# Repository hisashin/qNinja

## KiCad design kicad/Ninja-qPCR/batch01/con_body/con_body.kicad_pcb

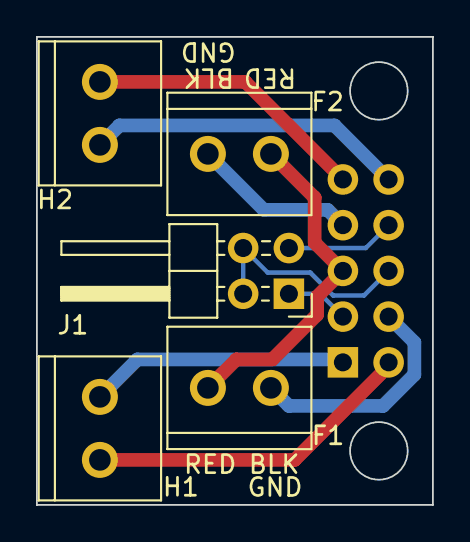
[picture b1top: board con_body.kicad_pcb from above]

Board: 2 copper layers, 22.0 x 26.0 mm, 6 parts (1 on the bottom side), 10 nets.

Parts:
F1, F2: Screw_Terminal_01x02; TB_SeeedOPL_320110028
H1, H2: Screw_Terminal_01x02; TB_SeeedOPL_320110028
J1: Conn_01x04_Male; Pin_Header_Angled_2x02_Pitch2.54mm
U1: Conn_02x05; Pin_Header_Straight_2x05_Pitch2.54mm

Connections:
FAN_BLACK_GND1: F1.2, U1.4
FAN_BLACK_GND2: F2.2, U1.7
FAN_RED_VCC: F1.1, F2.1, U1.5
GND: J1.2, J1.4, U1.6
HEATER1A: H1.1, U1.1
HEATER1B: H1.2, U1.2
HEATER2A: H2.1, U1.9
HEATER2B: H2.2, U1.10
THERM_EXT3: J1.3, U1.8
THERM_WELL: J1.1, U1.3

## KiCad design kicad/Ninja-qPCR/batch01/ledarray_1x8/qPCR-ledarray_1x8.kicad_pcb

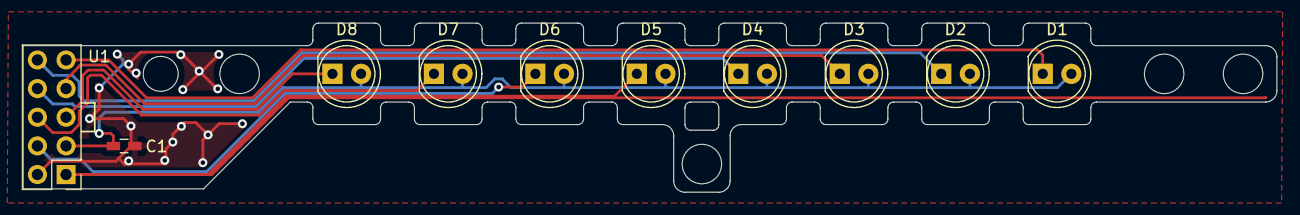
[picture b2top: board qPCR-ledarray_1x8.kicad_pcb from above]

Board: 2 copper layers, 111.2 x 15.0 mm, 10 parts (0 on the bottom side), 10 nets.

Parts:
C1: C; C_0603_HandSoldering
D1, D2, D3, D4, D5, D6, D7, D8: LED; LED_D5.0mm
U1: Conn_02x05; Pin_Header_Straight_2x05_Pitch2.54mm

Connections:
GND: C1.2, U1.2
OUT1: D1.1, U1.9
OUT2: D2.1, U1.10
OUT3: D3.1, U1.7
OUT4: D4.1, U1.8
OUT5: D5.1, U1.1
OUT6: D6.1, U1.4
OUT7: D7.1, U1.6
OUT8: D8.1, U1.5
VCC: C1.1, D1.2, D2.2, D3.2, D4.2, D5.2, D6.2, D7.2, D8.2, U1.3

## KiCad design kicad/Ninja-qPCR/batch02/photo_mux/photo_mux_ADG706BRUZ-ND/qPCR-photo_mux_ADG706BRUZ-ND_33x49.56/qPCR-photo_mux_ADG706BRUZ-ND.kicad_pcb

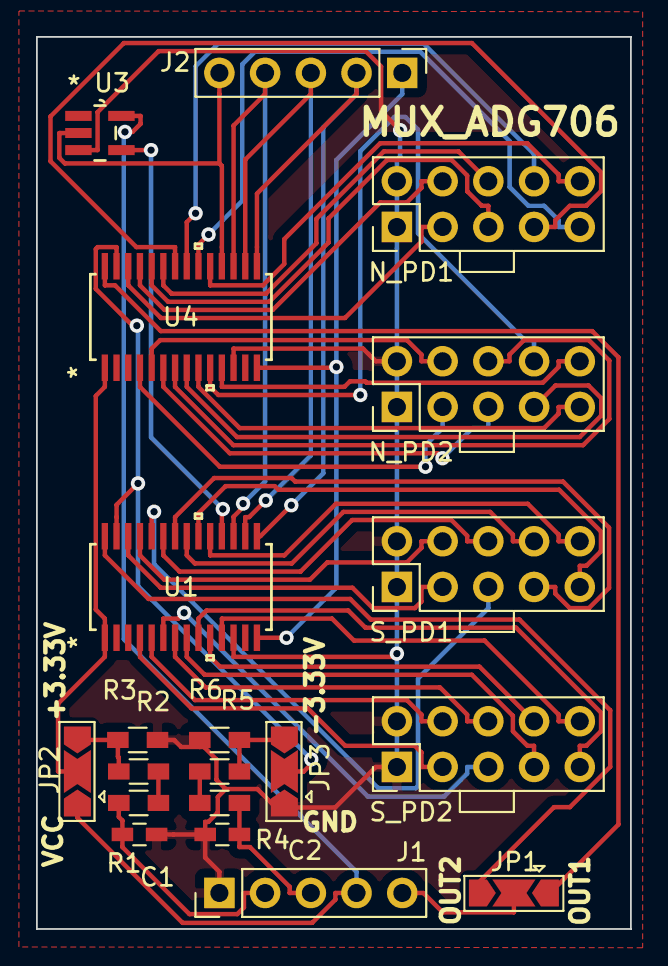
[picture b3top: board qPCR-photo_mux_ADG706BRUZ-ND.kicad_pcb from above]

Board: 2 copper layers, 33.0 x 49.6 mm, 20 parts (0 on the bottom side), 51 nets.

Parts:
C1, C2: C; C_0603_HandSoldering
J1, J2: Conn_01x05_Male; Pin_Header_Straight_1x05_Pitch2.54mm
JP1, JP2, JP3: Jumper_3_Open; SolderJumper-3_P2.0mm_Open_TrianglePad1.0x1.5mm
N_PD1, N_PD2: Conn_02x05; Con_2x05
R1, R2, R3, R4, R5, R6: R; R_0603_HandSoldering
S_PD1, S_PD2: Conn_02x05; Con_2x05
U1, U4: ADG706BRUZ
U3: SN74LVC1G04DBVR

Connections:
+10V: C1.1, J1.2, R1.1
-10V: C2.1, J1.3, R4.1
/+3.33V: JP2.3, R2.2, R3.1
/-3.33V: JP3.3, R5.2, R6.1
/MUX_SELECT_INV: U1.18, U3.4
/PD_MUX_OUT1: JP1.1, U4.28
/PD_MUX_OUT2: JP1.3, U1.28
/VDD: JP2.2, U1.1, U4.1
/VSS: JP3.2, U1.27, U4.27
ADDRESSA0: J2.4, U1.17, U4.17
ADDRESSA1: J2.3, U1.16, U4.16
ADDRESSA2: J2.2, U1.15, U4.15
ADDRESSA3: J2.1, U1.14, U4.14
GND: C1.2, C2.2, J1.1, JP3.1, N_PD1.1, N_PD1.2, N_PD2.1, N_PD2.2, R3.2, R6.2, S_PD1.1, S_PD1.2, S_PD2.1, S_PD2.2, U1.12, U3.3, U4.12
MUX_SELECT: J2.5, U3.2, U4.18
N_PD1_OUT1: N_PD1.10, U4.19
N_PD1_OUT2: N_PD1.9, U4.20
N_PD1_OUT3: N_PD1.8, U4.21
N_PD1_OUT4: N_PD1.7, U4.22
N_PD1_OUT5: N_PD1.6, U4.23
N_PD1_OUT6: N_PD1.5, U4.24
N_PD1_OUT7: N_PD1.4, U4.25
N_PD1_OUT8: N_PD1.3, U4.26
N_PD1_OUT9: N_PD2.10, U4.11
N_PD1_OUT10: N_PD2.8, U4.10
N_PD1_OUT11: N_PD2.9, U4.9
N_PD1_OUT12: N_PD2.7, U4.8
N_PD1_OUT13: N_PD2.6, U4.7
N_PD1_OUT14: N_PD2.5, U4.6
N_PD1_OUT15: N_PD2.4, U4.5
N_PD1_OUT16: N_PD2.3, U4.4
unnamed: R1.2, R2.1
unnamed: R4.2, R5.1
PD_MUX_OUT: J1.5, JP1.2
S_PD1_OUT1: S_PD1.10, U1.19
S_PD1_OUT2: S_PD1.9, U1.20
S_PD1_OUT3: S_PD1.8, U1.21
S_PD1_OUT4: S_PD1.7, U1.22
S_PD1_OUT5: S_PD1.6, U1.23
S_PD1_OUT6: S_PD1.5, U1.24
S_PD1_OUT7: S_PD1.4, U1.25
S_PD1_OUT8: S_PD1.3, U1.26
S_PD1_OUT9: S_PD2.10, U1.11
S_PD1_OUT10: S_PD2.8, U1.10
S_PD1_OUT11: S_PD2.9, U1.9
S_PD1_OUT12: S_PD2.7, U1.8
S_PD1_OUT13: S_PD2.6, U1.7
S_PD1_OUT14: S_PD2.5, U1.6
S_PD1_OUT15: S_PD2.4, U1.5
S_PD1_OUT16: S_PD2.3, U1.4
VCC_LOGIC: J1.4, JP2.1, U3.5

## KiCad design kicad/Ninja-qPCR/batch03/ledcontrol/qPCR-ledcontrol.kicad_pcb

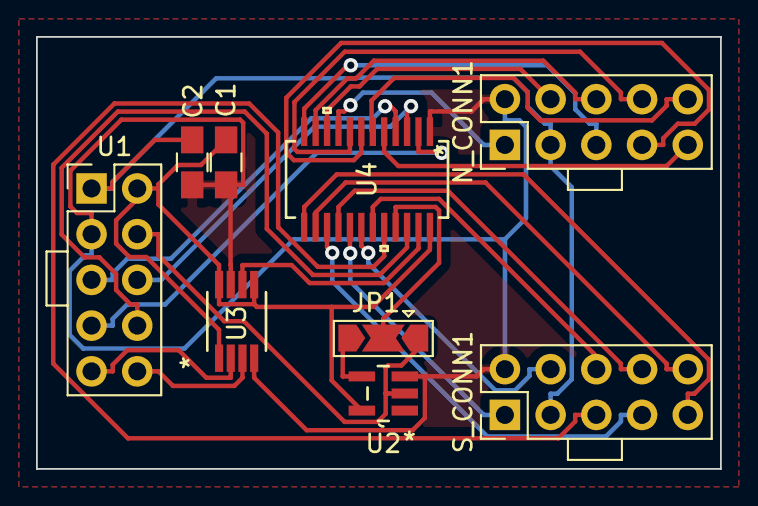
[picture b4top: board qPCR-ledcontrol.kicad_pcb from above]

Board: 2 copper layers, 38.0 x 24.0 mm, 9 parts (0 on the bottom side), 29 nets.

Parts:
C1, C2: C; C_0805_HandSoldering
JP1: Jumper_3_Open; SolderJumper-3_P2.0mm_Open_TrianglePad1.0x1.5mm
N_CONN1: Conn_02x05; Con_2x05
S_CONN1: Conn_02x05; Con_2x05
U1: Conn_02x05; Con_2x05
U2: SN74LVC1G04DBVR
U3: MCP4551T-502E_MS; MCP4551T-502E&slash_MS
U4: TLC59281DBQR

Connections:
/LED_IREF: U3.6, U4.23
GND: C1.2, C2.2, N_CONN1.2, S_CONN1.2, U1.3, U2.3, U3.4, U3.7, U4.1
I2C_SCL: U1.9, U3.2
I2C_SDA: U1.10, U3.3
LED_BLANK: JP1.2, U4.21
LED_LAT: U1.5, U4.4
LED_PWM: JP1.1, U1.4, U2.2
LED_SPI_MISO: U1.8, U4.22
LED_SPI_MOSI: U1.7, U4.2
LED_SPI_SCLK: U1.6, U4.3
N_LED_OUT1: N_CONN1.9, U4.5
N_LED_OUT2: N_CONN1.10, U4.6
N_LED_OUT3: N_CONN1.7, U4.7
N_LED_OUT4: N_CONN1.8, U4.8
N_LED_OUT5: N_CONN1.1, U4.9
N_LED_OUT6: N_CONN1.4, U4.10
N_LED_OUT7: N_CONN1.6, U4.11
N_LED_OUT8: N_CONN1.5, U4.12
unnamed: JP1.3, U2.4
S_LED_OUT1: S_CONN1.9, U4.13
S_LED_OUT2: S_CONN1.10, U4.14
S_LED_OUT3: S_CONN1.7, U4.15
S_LED_OUT4: S_CONN1.8, U4.16
S_LED_OUT5: S_CONN1.1, U4.17
S_LED_OUT6: S_CONN1.4, U4.18
S_LED_OUT7: S_CONN1.6, U4.19
S_LED_OUT8: S_CONN1.5, U4.20
VCC_LED: C2.1, N_CONN1.3, S_CONN1.3, U1.1
VCC_LOGIC: C1.1, U1.2, U2.5, U3.1, U3.5, U3.8, U4.24

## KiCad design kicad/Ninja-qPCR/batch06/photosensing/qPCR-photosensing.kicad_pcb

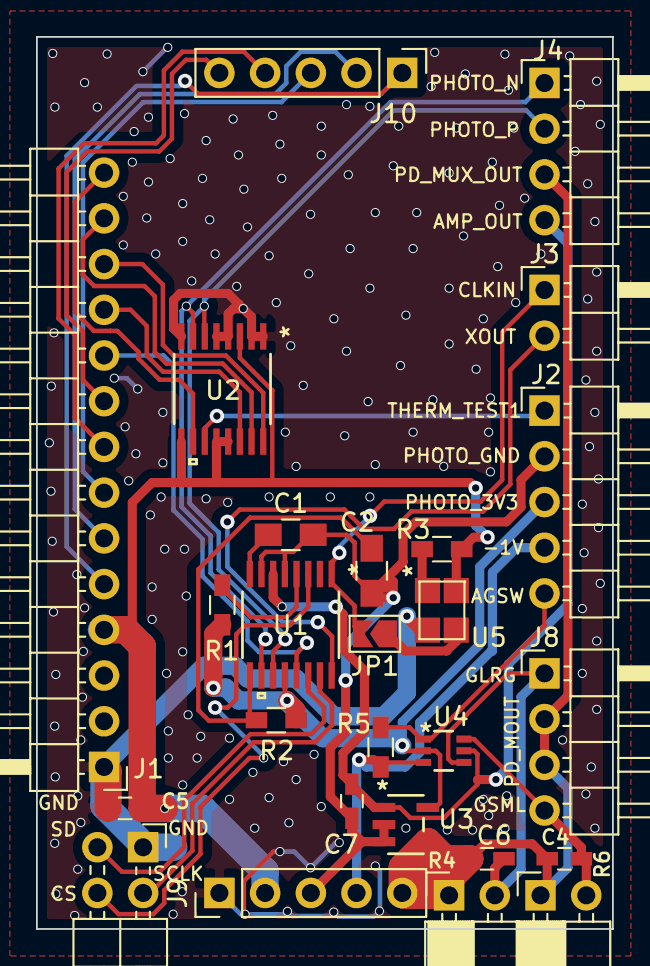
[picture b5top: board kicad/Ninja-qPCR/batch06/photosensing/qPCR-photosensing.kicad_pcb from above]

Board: 2 copper layers, 32.0 x 49.6 mm, 26 parts (0 on the bottom side), 33 nets.

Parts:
C1: 1uF; C_0805_HandSoldering
C2: 10uF; C_0805_HandSoldering
C4, C6: 22pF; C_0603_HandSoldering
C5, C7: 0.1uF; C_0603_HandSoldering
J1: Conn_01x14_Male; Pin_Header_Angled_1x14_Pitch2.54mm
J2: Conn_01x05_Male; Pin_Header_Angled_1x05_Pitch2.54mm
J3: Conn_01x02_Male; Pin_Header_Angled_1x02_Pitch2.54mm
J4, J8: Conn_01x04_Male; Pin_Header_Angled_1x04_Pitch2.54mm
J9, J10: Conn_01x05_Female; Pin_Header_Straight_1x05_Pitch2.54mm
JP1: Jumper; SolderJumper-2_P1.3mm_Open_TrianglePad1.0x1.5mm
JSPI1: Conn_01x04_Male; Pin_Header_Angled_2x02_Pitch2.54mm
R1, R2, R3: 10K; R_0603_HandSoldering
R4, R6: R; Socket_Strip_Angled_1x02_Pitch2.54mm
R5: R; R_0603_HandSoldering
U1: ADA2200ARUZ
U2: ADS1219IPWR
U3: AD8605ARTZ-R2
U4: TS5A9411DCKR
U5: COM1305-0.032768-EXT-T-TR

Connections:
-1V: J2.4, J9.4, R5.2, U4.3
/AMP_GAIN_SW: J2.5, R5.1, U4.1
/AMP_OUT: C7.2, J4.4, U1.6, U3.1, U4.5
/GAIN_LARGE: C6.1, J8.1, R4.2, U4.4
/GAIN_SMALL: C4.1, J8.4, R6.2, U4.6
/PHOTO_OUT_N: J4.1, U1.10, U2.7
/PHOTO_OUT_P: J4.2, U1.11, U2.6
ADC_DRDY: J1.11, U2.14
CLKIN: J3.1, JP1.2, U1.1
DEMOD_SPI_CS: JSPI1.4, U1.3
DEMOD_SPI_SCLK: JSPI1.2, U1.15
DEMOD_SPI_SDIO: JSPI1.3, U1.14
GND: C5.2, J1.1, J9.1, JSPI1.1, U2.1, U2.2, U2.4, U2.5, U2.8, U5.2
I2C_SCL: J1.12, U2.16
I2C_SDA: J1.13, U2.15
unnamed: C1.1, U1.8
unnamed: C2.1, R2.1, U1.9
unnamed: JP1.1, U5.3
unnamed: R1.1, U1.4
unnamed: R3.1, U5.1
PD_MUX_GPIO1: J1.9, J10.5
PD_MUX_GPIO2: J1.8, J10.4
PD_MUX_GPIO3: J1.7, J10.3
PD_MUX_GPIO4: J1.6, J10.2
PD_MUX_GPIO5: J1.5, J10.1
PD_MUX_OUT: C4.2, C6.2, J4.3, J8.2, J8.3, J9.5, R4.1, R6.1, U3.4
PD_REF_PWM: J1.10, U1.13
PHOTO_3V3: J2.3, R1.2, R2.2, U1.12, U3.5, U4.2
PHOTO_GND: C1.2, C2.2, C7.1, J2.2, J9.3, U1.5, U1.7, U3.2, U3.3
THERM_TEST1: J2.1, U2.11
THERM_WELL: J1.14, U2.10
VCC_LOGIC: C5.1, J1.4, J9.2, R3.2, U2.3, U2.9, U2.12, U2.13, U5.4
XOUT: J3.2, U1.16

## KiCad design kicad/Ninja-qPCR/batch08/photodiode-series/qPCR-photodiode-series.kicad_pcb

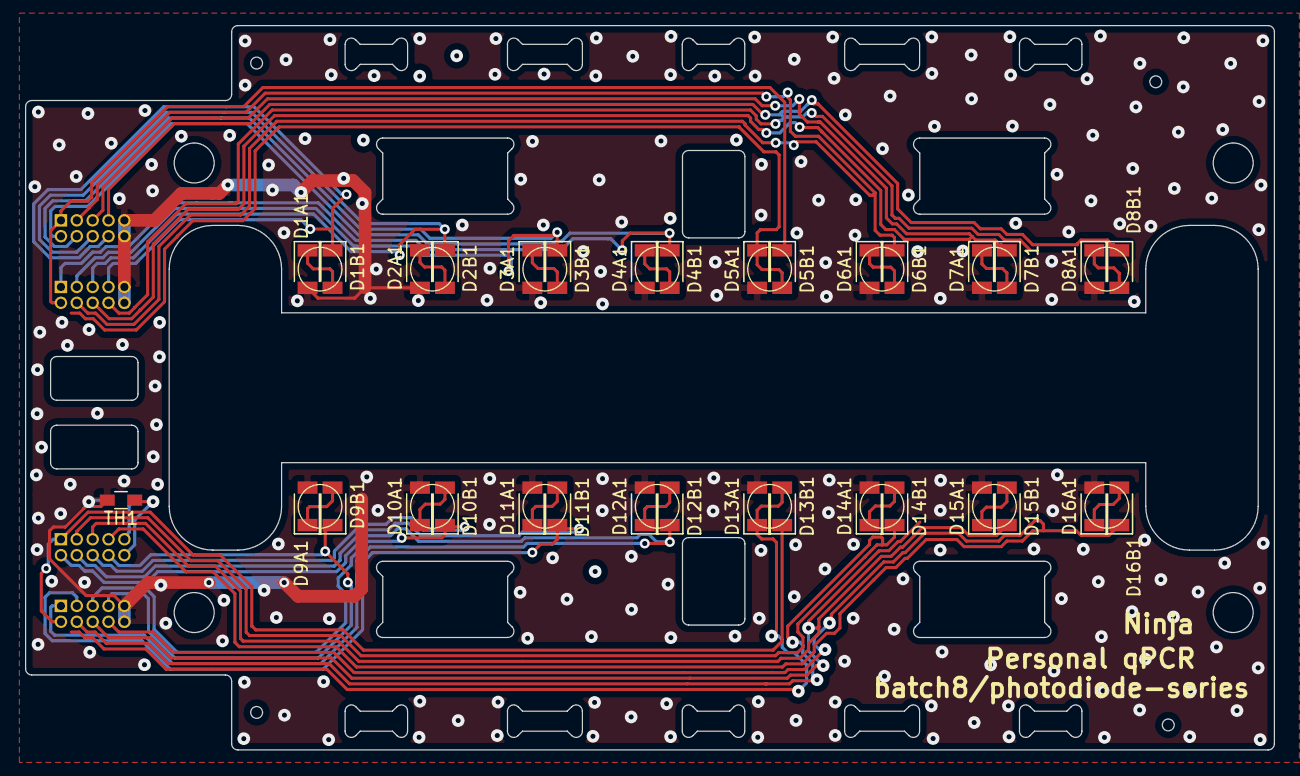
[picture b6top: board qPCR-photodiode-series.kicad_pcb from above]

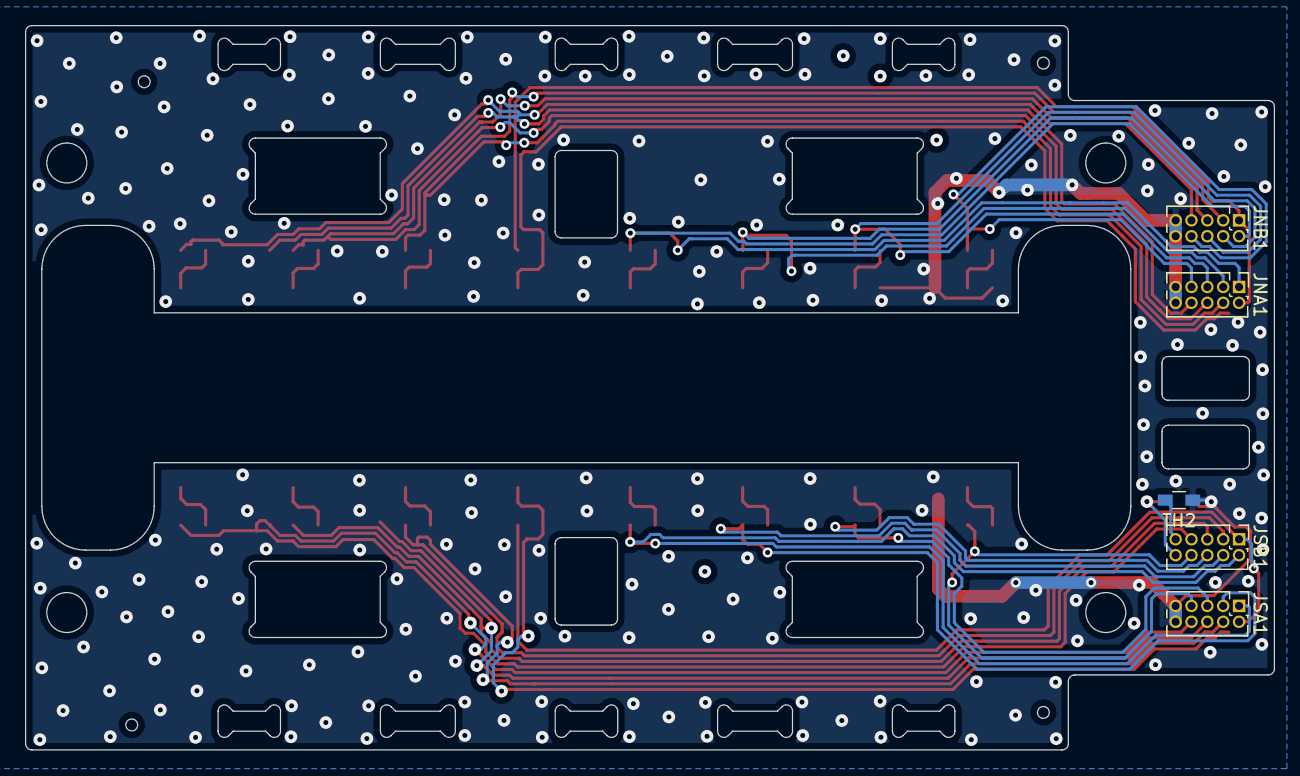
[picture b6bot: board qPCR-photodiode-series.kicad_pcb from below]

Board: 2 copper layers, 100.0 x 58.0 mm, 38 parts (5 on the bottom side), 35 nets.

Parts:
D1A1, D1B1, D2A1, D2B1, D3A1, D3B1, D4A1, D4B1, D5A1, D5B1, D6A1, D6B1, D7A1, D7B1, D8A1, D8B1, D9A1, D9B1, D10A1, D10B1, D11A1, D11B1, D12A1, D12B1, D13A1, D13B1, D14A1, D14B1, D15A1, D15B1, D16A1, D16B1: D_Photo; D_1206
JNA1: Conn_01x10_Male; Pin_Header_Straight_2x05_Pitch1.27mm
JNB1: Conn_01x10_Male; Pin_Header_Straight_2x05_Pitch1.27mm
JSA1: Conn_01x10_Male; Pin_Header_Straight_2x05_Pitch1.27mm
JSB1: Conn_01x10_Male; Pin_Header_Straight_2x05_Pitch1.27mm
TH1, TH2: Thermistor; R_0603_HandSoldering

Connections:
/N_PD_OUT1: D1B1.1, JNA1.7, JNB1.8
/N_PD_OUT3: D2B1.1, JNA1.5, JNB1.6
/N_PD_OUT5: D3B1.1, JNA1.3, JNB1.4
/N_PD_OUT7: D4B1.1, JNA1.1, JNB1.2
/N_PD_OUT9: D5B1.1, JNA1.2, JNB1.1
/N_PD_OUT11: D6B1.1, JNA1.4, JNB1.3
/N_PD_OUT13: D7B1.1, JNA1.6, JNB1.5
/N_PD_OUT15: D8B1.1, JNA1.8, JNB1.7
/S_PD_OUT1: D9B1.1, JSA1.7, JSB1.8
/S_PD_OUT3: D10B1.1, JSA1.5, JSB1.6
/S_PD_OUT5: D11B1.1, JSA1.3, JSB1.4
/S_PD_OUT7: D12B1.1, JSA1.1, JSB1.2
/S_PD_OUT9: D13B1.1, JSA1.2, JSB1.1
/S_PD_OUT11: D14B1.1, JSA1.4, JSB1.3
/S_PD_OUT13: D15B1.1, JSA1.6, JSB1.5
/S_PD_OUT15: D16B1.1, JSA1.8, JSB1.7
GNDA: D1A1.2, D2A1.2, D3A1.2, D4A1.2, D5A1.2, D6A1.2, D7A1.2, D8A1.2, D9A1.2, D10A1.2, D11A1.2, D12A1.2, D13A1.2, D14A1.2, D15A1.2, D16A1.2, JNA1.9, JNA1.10, JNB1.9, JNB1.10, JSA1.9, JSA1.10, TH1.2, TH2.2
unnamed: D1A1.1, D1B1.2
unnamed: D2A1.1, D2B1.2
unnamed: D3A1.1, D3B1.2
unnamed: D4A1.1, D4B1.2
unnamed: D5A1.1, D5B1.2
unnamed: D6A1.1, D6B1.2
unnamed: D7A1.1, D7B1.2
unnamed: D8A1.1, D8B1.2
unnamed: D9A1.1, D9B1.2
unnamed: D10A1.1, D10B1.2
unnamed: D11A1.1, D11B1.2
unnamed: D12A1.1, D12B1.2
unnamed: D13A1.1, D13B1.2
unnamed: D14A1.1, D14B1.2
unnamed: D15A1.1, D15B1.2
unnamed: D16A1.1, D16B1.2
unnamed: JSB1.9, TH2.1
unnamed: JSB1.10, TH1.1

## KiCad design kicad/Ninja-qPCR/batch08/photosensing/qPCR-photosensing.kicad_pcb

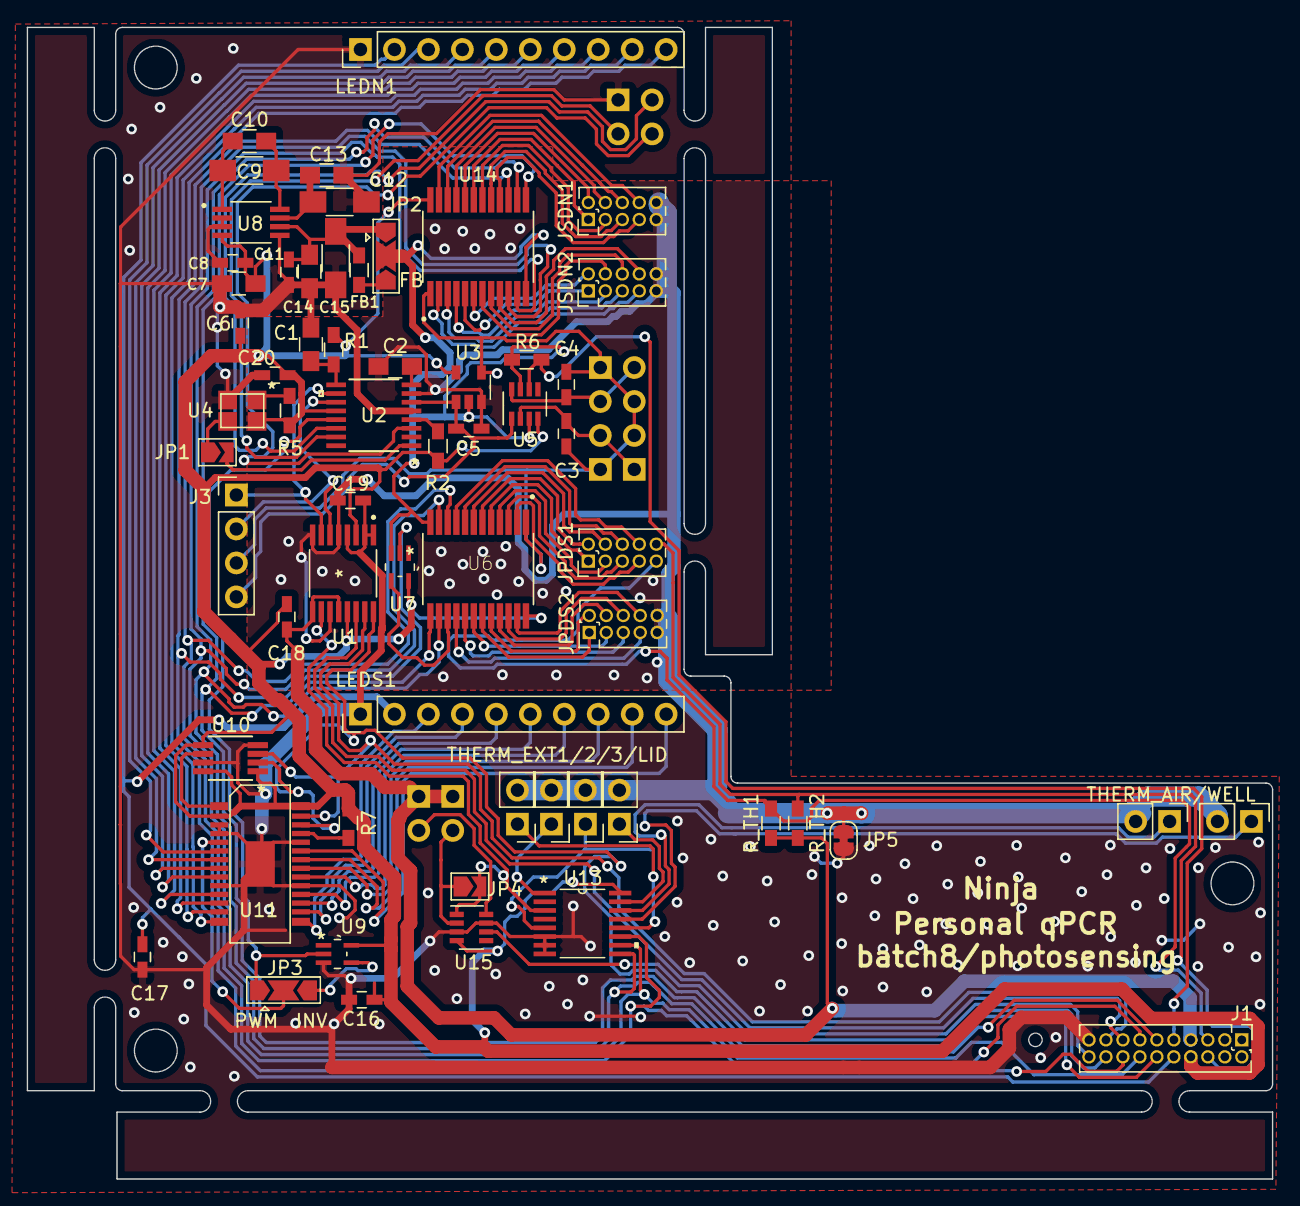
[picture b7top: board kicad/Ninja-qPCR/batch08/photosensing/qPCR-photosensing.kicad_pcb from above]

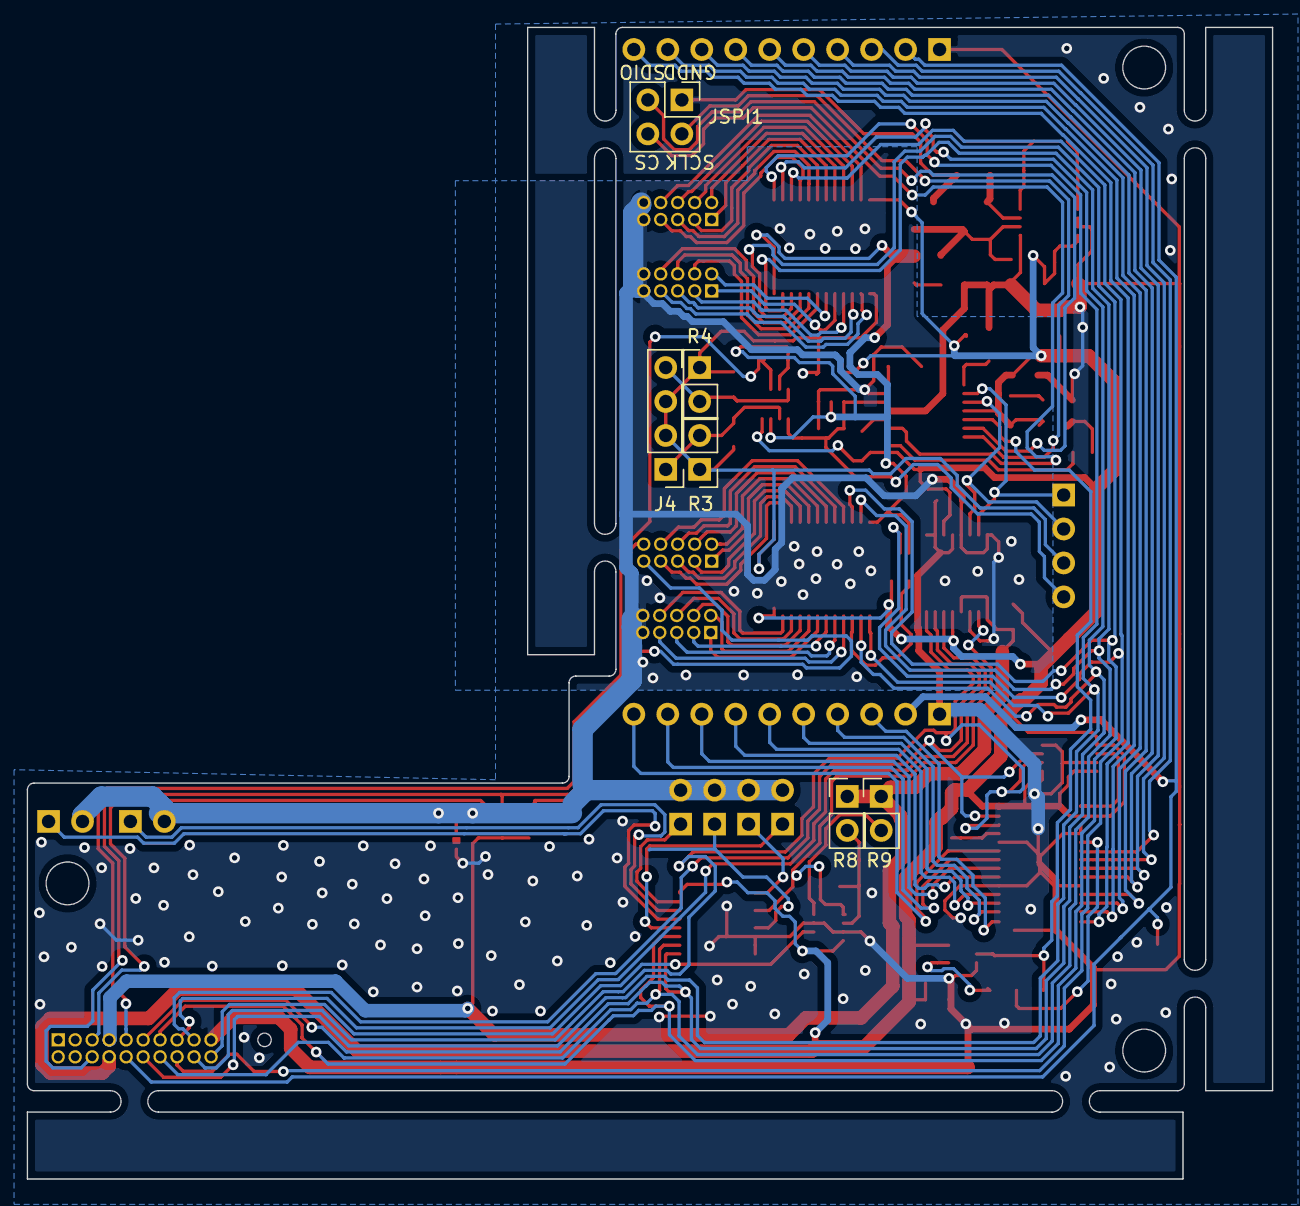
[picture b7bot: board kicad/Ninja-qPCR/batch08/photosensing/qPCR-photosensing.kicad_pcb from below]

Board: 2 copper layers, 93.1 x 86.1 mm, 67 parts (6 on the bottom side), 101 nets.

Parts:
C1, C2, C7, C10, C13: 4.7uF; C_0805_HandSoldering
C3, C4: 22pF; C_0603_HandSoldering
C5, C6, C8, C11, C16, C17, C18, C19, C20: 0.1uF; C_0603_HandSoldering
C9, C12, C15: DNP; C_1206_HandSoldering
C14: 22uF; C_0805_HandSoldering
FB1: 120@100MHz; R_0603_HandSoldering
J1: Conn_01x20_Male; Pin_Header_Straight_2x10_Pitch1.27mm
J3, J4: Conn_01x04_Male; Pin_Header_Straight_1x04_Pitch2.54mm
JP1: Jumper; SolderJumper-2_P1.3mm_Open_TrianglePad1.0x1.5mm
JP2, JP3: Jumper_3_Open; SolderJumper-3_P2.0mm_Open_TrianglePad1.0x1.5mm
JP4: Jumper_2_Open; SolderJumper-2_P1.3mm_Open_TrianglePad1.0x1.5mm
JP5: SolderJumper_2_Bridged; SolderJumper-2_P1.3mm_Bridged_RoundedPad1.0x1.5mm
JPDS1, JPDS2: Conn_01x10_Male; Pin_Header_Straight_2x05_Pitch1.27mm
JSDN1, JSDN2: Conn_01x10_Male; Pin_Header_Straight_2x05_Pitch1.27mm
JSPI1: Conn_01x04_Male; Pin_Header_Straight_2x02_Pitch2.54mm
LEDN1: Conn_01x10_Male; Pin_Header_Straight_1x10_Pitch2.54mm
LEDS1: Conn_01x10_Male; Pin_Header_Straight_1x10_Pitch2.54mm
R1, R2, R5, R6: 10K; R_0603_HandSoldering
R3, R4: R; Pin_Header_Straight_1x02_Pitch2.54mm
R7: 47k; R_0603_HandSoldering
R8, R9: ?k; Pin_Header_Straight_1x02_Pitch2.54mm
R_TH1, R_TH2: 10K; R_0603_HandSoldering
TAIR1: Conn_01x02_Male; Pin_Header_Straight_1x02_Pitch2.54mm
TEXT1, TEXT2, TEXT3: Conn_01x02_Male; Pin_Header_Straight_1x02_Pitch2.54mm
TLID1: Conn_01x02_Male; Pin_Header_Straight_1x02_Pitch2.54mm
TWELL1: Conn_01x02_Male; Pin_Header_Straight_1x02_Pitch2.54mm
U1: ADS122C04IPWR
U2: ADA2200ARUZ
U3: LMP7717MF_NOPB; SOT-23-5
U4: COM1305-0.032768-EXT-T-TR
U5, U15: TS12A12511DCNR; SOT-23-8
U6, U14: CD74HC4067M96; SOP65P780X200-24N
U7, U9: SN74LVC1GU04DCKR
U8: LM7705MMX_NOPB; LM7705MMX-NOPB
U10: MCP4551T-503E/MS; MCP4551T-502E&slash_MS
U11: PCA9955B
U13: SN74LV4051APWR

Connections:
3V3A: C18.1, J1.7, R8.1, R9.1, R_TH1.2, R_TH2.2, U1.9, U1.12
3V3D: C6.1, C7.2, C8.2, C16.1, C18.2, C20.1, J1.8, R1.2, R2.2, R5.2, R7.2, U1.3, U1.13, U2.12, U3.5, U4.4, U5.4, U6.24, U7.5, U8.4, U9.5, U10.1, U10.5, U10.8, U11.2, U11.28, U13.16, U14.24, U15.4
-1V: JP2.2, R6.2, U3.2, U5.3, U5.7, U6.12, U7.3, U14.12
/AMP_OUT: C5.2, J3.4, U2.6, U3.1, U5.1
/GAIN_LARGE: C3.1, J4.1, R3.2, U5.2
/GAIN_SMALL: C4.1, J4.4, R4.2, U5.8
/LED/LED_BLANK: JP3.2, U11.5
/LED/LED_IREF: U10.6, U11.1
/PHOTO_OUT_N: J3.1, U1.7, U2.10
/PHOTO_OUT_P: J3.2, U1.6, U2.11
/Sheet60AF0517/MUX_SELECT_INV: U6.15, U7.4
/Sheet60AF0517/S_PD_OUT1: JPDS2.8, U6.23
/Sheet60AF0517/S_PD_OUT2: JPDS1.7, U6.2
/Sheet60AF0517/S_PD_OUT3: JPDS2.6, U6.22
/Sheet60AF0517/S_PD_OUT4: JPDS1.5, U6.3
/Sheet60AF0517/S_PD_OUT5: JPDS2.4, U6.21
/Sheet60AF0517/S_PD_OUT6: JPDS1.3, U6.4
/Sheet60AF0517/S_PD_OUT7: JPDS2.2, U6.20
/Sheet60AF0517/S_PD_OUT8: JPDS1.1, U6.5
/Sheet60AF0517/S_PD_OUT9: JPDS2.1, U6.19
/Sheet60AF0517/S_PD_OUT10: JPDS1.2, U6.6
/Sheet60AF0517/S_PD_OUT11: JPDS2.3, U6.18
/Sheet60AF0517/S_PD_OUT12: JPDS1.4, U6.7
/Sheet60AF0517/S_PD_OUT13: JPDS2.5, U6.17
/Sheet60AF0517/S_PD_OUT14: JPDS1.6, U6.8
/Sheet60AF0517/S_PD_OUT15: JPDS2.7, U6.16
/Sheet60AF0517/S_PD_OUT16: JPDS1.8, U6.9
/Sheet60C04E5B/N_PD_OUT1: JSDN2.8, U14.9
/Sheet60C04E5B/N_PD_OUT2: JSDN1.7, U14.16
/Sheet60C04E5B/N_PD_OUT3: JSDN2.6, U14.8
/Sheet60C04E5B/N_PD_OUT4: JSDN1.5, U14.17
/Sheet60C04E5B/N_PD_OUT5: JSDN2.4, U14.7
/Sheet60C04E5B/N_PD_OUT6: JSDN1.3, U14.18
/Sheet60C04E5B/N_PD_OUT7: JSDN2.2, U14.6
/Sheet60C04E5B/N_PD_OUT8: JSDN1.1, U14.19
/Sheet60C04E5B/N_PD_OUT9: JSDN2.1, U14.5
/Sheet60C04E5B/N_PD_OUT10: JSDN1.2, U14.20
/Sheet60C04E5B/N_PD_OUT11: JSDN2.3, U14.4
/Sheet60C04E5B/N_PD_OUT12: JSDN1.4, U14.21
/Sheet60C04E5B/N_PD_OUT13: JSDN2.5, U14.3
/Sheet60C04E5B/N_PD_OUT14: JSDN1.6, U14.22
/Sheet60C04E5B/N_PD_OUT15: JSDN2.7, U14.2
/Sheet60C04E5B/N_PD_OUT16: JSDN1.8, U14.23
ADC_DRDY: J1.15, U1.14
AMP_GAIN_SW: J1.9, R6.1, U5.6
CLKIN: JP1.2, U2.1
DEMOD_SPI_CS: JSPI1.4, U2.3
DEMOD_SPI_SCLK: JSPI1.2, U2.15
DEMOD_SPI_SDIO: JSPI1.3, U2.14
GNDA: C2.2, C5.1, C19.1, JP5.2, JPDS2.9, JPDS2.10, JSDN1.9, JSDN1.10, JSDN2.9, JSDN2.10, TAIR1.2, TEXT1.2, TEXT2.2, TEXT3.2, TLID1.2, TWELL1.2, U1.5, U1.8, U1.11, U2.7, U3.3
GNDD: C1.2, C6.2, C7.1, C8.1, C11.1, C12.1, C13.1, C14.1, C15.1, C16.2, C17.2, C19.2, C20.2, J1.19, JP5.1, JSPI1.1, LEDN1.1, LEDS1.1, U1.1, U1.2, U1.4, U2.5, U4.2, U8.2, U8.3, U8.5, U9.3, U10.4, U10.7, U11.3, U11.4, U11.10, U11.19, U11.24, U11.29, U13.6, U13.7, U13.8, U15.3, U15.7
I2C_SCL: J1.18, U1.16, U10.2, U11.26
I2C_SDA: J1.17, U1.15, U10.3, U11.27
MUX_S0: J1.13, U6.10, U13.11, U14.10
MUX_S1: J1.14, U6.11, U13.10, U14.11
MUX_S2: J1.11, U6.14, U13.9, U14.14
MUX_S3: J1.12, U6.13, U14.13
MUX_SELECT: J1.16, U7.2, U14.15
N_LED_OUT1: LEDN1.3, U11.6
N_LED_OUT2: LEDN1.4, U11.7
N_LED_OUT3: LEDN1.5, U11.8
N_LED_OUT4: LEDN1.6, U11.9
N_LED_OUT5: LEDN1.7, U11.11
N_LED_OUT6: LEDN1.8, U11.12
N_LED_OUT7: LEDN1.9, U11.13
N_LED_OUT8: LEDN1.10, U11.14
unnamed: C1.1, R1.1, U2.9
unnamed: C2.1, U2.8
unnamed: C9.1, C10.1, U8.8
unnamed: C9.2, C10.2, U8.1
unnamed: C11.2, C14.2, C15.2, FB1.2, JP2.1, U8.6
unnamed: C12.2, C13.2, U8.7
unnamed: FB1.1, JP2.3
unnamed: JP1.1, U4.3
unnamed: JP3.3, U9.4
unnamed: JP4.1, R8.2, U15.2
unnamed: R2.1, U2.4
unnamed: R5.1, U4.1
unnamed: R7.1, U11.25
unnamed: R9.2, U15.8
PD_MUX_OUT: C3.2, C4.2, J3.3, J4.2, J4.3, R3.1, R4.1, U3.4, U6.1, U14.1
PD_REF_PWM: JP3.1, U2.13, U9.2
PD_TH1: J1.5, JPDS1.9, R_TH1.1
PD_TH2: J1.6, JPDS1.10, R_TH2.1
S_LED_OUT1: LEDS1.3, U11.15
S_LED_OUT2: LEDS1.4, U11.16
S_LED_OUT3: LEDS1.5, U11.17
S_LED_OUT4: LEDS1.6, U11.18
S_LED_OUT5: LEDS1.7, U11.20
S_LED_OUT6: LEDS1.8, U11.21
S_LED_OUT7: LEDS1.9, U11.22
S_LED_OUT8: LEDS1.10, U11.23
THERM_AIR: TAIR1.1, U13.14
THERM_EXT1: TEXT1.1, U13.12
THERM_EXT2: TEXT2.1, U13.1
THERM_EXT3: TEXT3.1, U13.5
THERM_LID: TLID1.1, U13.15
THERM_MUX_OUT: JP4.2, U1.10, U13.3, U15.1
THERM_R_SWITCH: J1.20, U15.6
THERM_WELL: TWELL1.1, U13.13
VCC_LED: C17.1, J1.10, LEDN1.2, LEDS1.2

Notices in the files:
parts and their libraries:
Copyright 2016 Accelerated Designs. All rights reserved.
Copyright 2021 Accelerated Designs. All rights reserved.
